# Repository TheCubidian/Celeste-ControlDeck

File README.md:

# Celeste-ControlDeck

Did you ever play Celeste with arrow keys? Hated it because those were the default keybinds?
The Celeste ControlDeck vanquishes this issue, by giving you a dedicated 7 keys to replace those arrow keys.

## BOM
- 8x SK6812MINI-E
- 1x SSD1306 0.91" 128x32 OLED
- 1x Seeed XIAO RP2040
- 7x MX-Style Switches
- 7x White DSA Keycaps

Case composed of Top.step and Bottom.step.

Schematic                  |  PCB                      |  PCB Front Preview              |  PCB Back Preview
:-------------------------:|:-------------------------:|:-------------------------:|:-------------------------:|
  |        |   |  

Assembled Device           |  Case Components
:-------------------------:|:-------------------------:|
    |

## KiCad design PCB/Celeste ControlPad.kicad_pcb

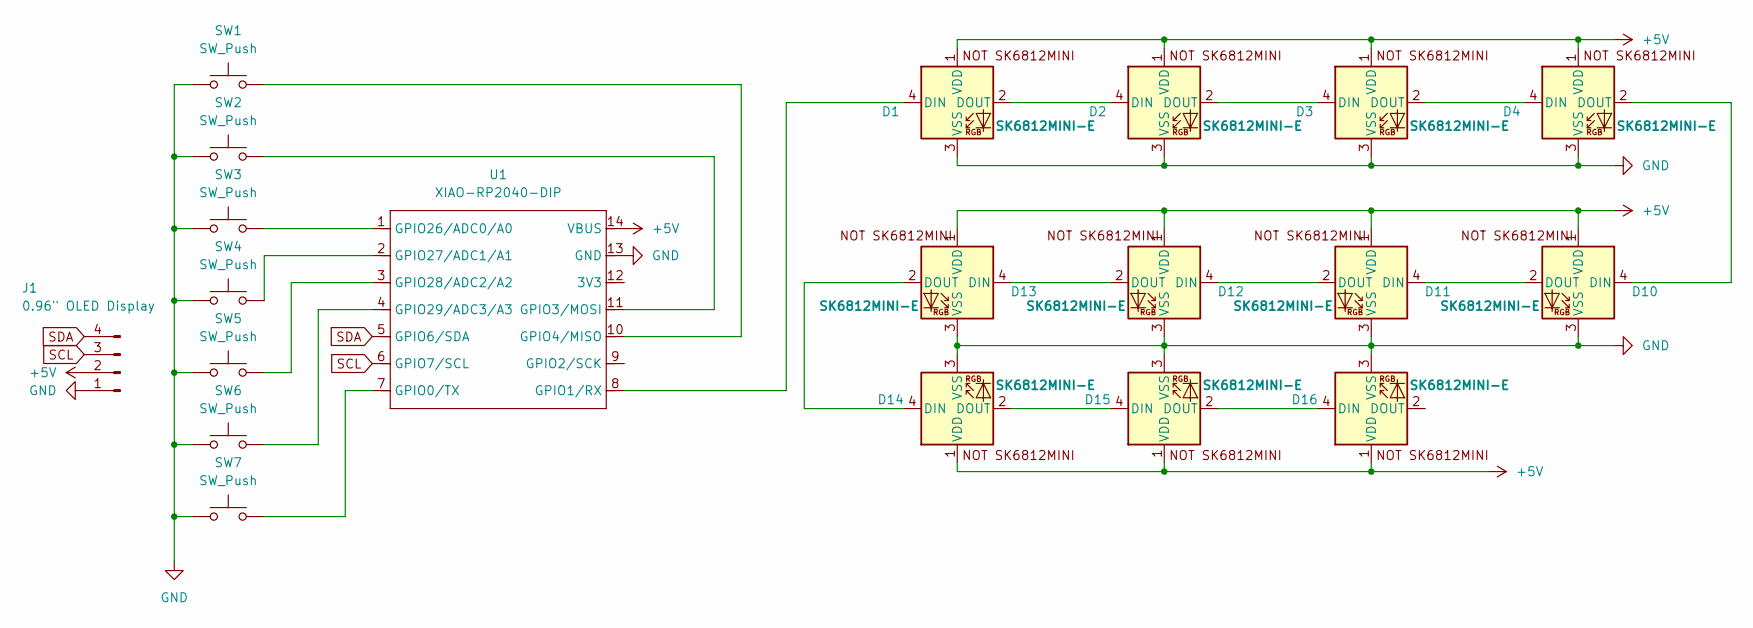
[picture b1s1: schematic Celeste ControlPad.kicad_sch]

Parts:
D1, D2, D3, D4, D10, D11, D12, D13, D14, D15, D16: SK6812MINI-E; SK6812MINI-E_fixed
J1: 0.96" OLED Display; SSD1306-0.91-OLED-4pin-128x32
SW1, SW2, SW3, SW4, SW5, SW6, SW7: SW_Push; SW_Cherry_MX_1.00u_PCB
U1: XIAO-RP2040-DIP

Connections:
+5V: D1.1 (VDD), D2.1 (VDD), D3.1 (VDD), D4.1 (VDD), D10.1 (VDD), D11.1 (VDD), D12.1 (VDD), D13.1 (VDD), D14.1 (VDD), D15.1 (VDD), D16.1 (VDD), J1.2, U1.14 (VBUS)
GND: D1.3 (VSS), D2.3 (VSS), D3.3 (VSS), D4.3 (VSS), D10.3 (VSS), D11.3 (VSS), D12.3 (VSS), D13.3 (VSS), D14.3 (VSS), D15.3 (VSS), D16.3 (VSS), J1.1, SW1.1, SW2.1, SW3.1, SW4.1, SW5.1, SW6.1, SW7.1, U1.13 (GND)
unnamed: D1.4 (DIN), U1.8 (GPIO1/RX)
unnamed: D1.2 (DOUT), D2.4 (DIN)
unnamed: D2.2 (DOUT), D3.4 (DIN)
unnamed: D3.2 (DOUT), D4.4 (DIN)
unnamed: D4.2 (DOUT), D10.4 (DIN)
unnamed: D10.2 (DOUT), D11.4 (DIN)
unnamed: D11.2 (DOUT), D12.4 (DIN)
unnamed: D12.2 (DOUT), D13.4 (DIN)
unnamed: D13.2 (DOUT), D14.4 (DIN)
unnamed: D14.2 (DOUT), D15.4 (DIN)
unnamed: D15.2 (DOUT), D16.4 (DIN)
unnamed: SW7.2, U1.7 (GPIO0/TX)
unnamed: SW2.2, U1.11 (GPIO3/MOSI)
unnamed: SW1.2, U1.10 (GPIO4/MISO)
unnamed: SW3.2, U1.1 (GPIO26/ADC0/A0)
unnamed: SW4.2, U1.2 (GPIO27/ADC1/A1)
unnamed: SW5.2, U1.3 (GPIO28/ADC2/A2)
unnamed: SW6.2, U1.4 (GPIO29/ADC3/A3)
SCL: J1.3, U1.6 (GPIO7/SCL)
SDA: J1.4, U1.5 (GPIO6/SDA)

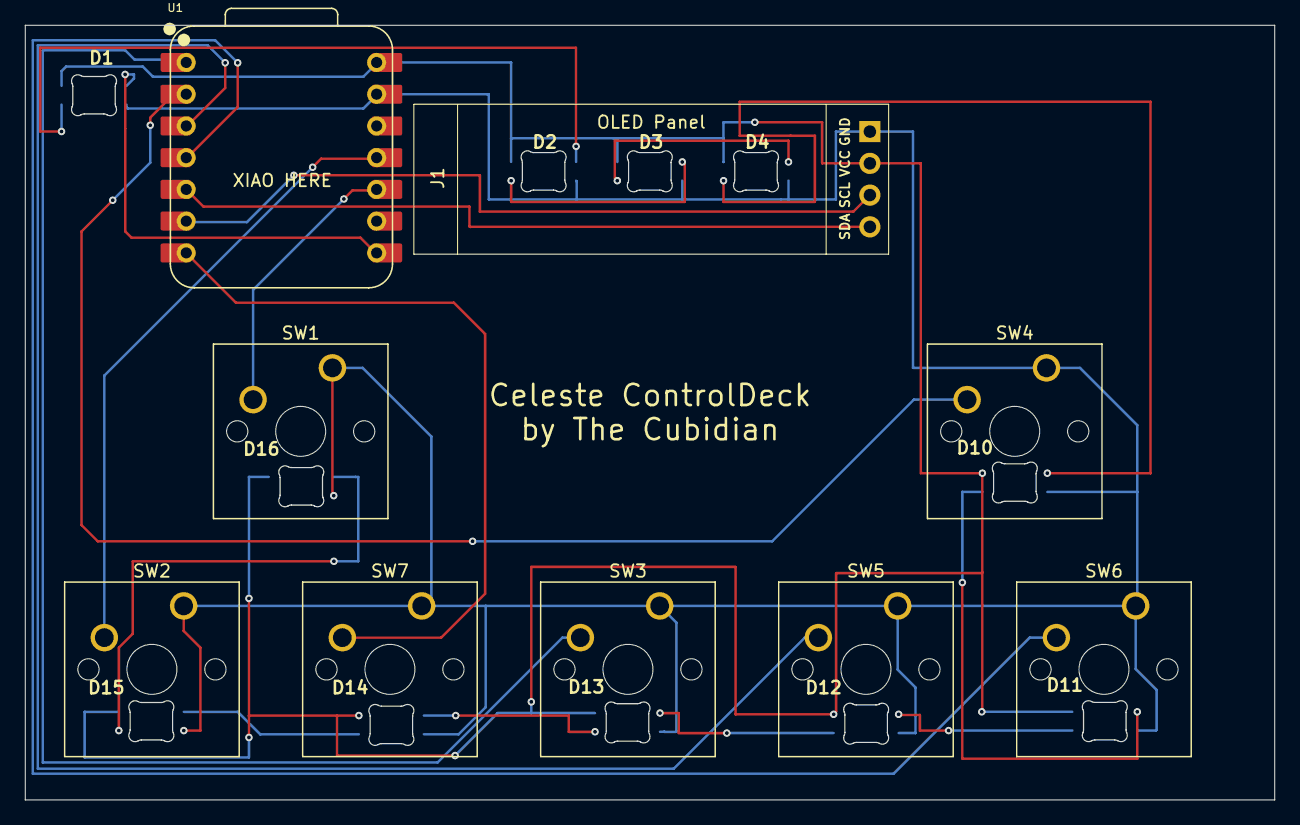
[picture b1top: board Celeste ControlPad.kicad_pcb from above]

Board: 2 copper layers, 100.0 x 62.0 mm, 20 parts (0 on the bottom side), 22 nets.

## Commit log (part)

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2026-02-07 Update README with electrical components list
    Added a section for electrical components used in the project.
2026-03-31 Rename project from ControlPad to ControlDeck
2026-03-31 Added all required files except firmware
2026-03-31 Added placeholders for folders
2026-03-31 Updated BOM
    Added BOM section and updated project description.
2026-03-31 Added image placeholders
2026-03-31 Update PCB images and add front/back previews
2026-03-31 Added all images
2026-03-31 Fixed image link
